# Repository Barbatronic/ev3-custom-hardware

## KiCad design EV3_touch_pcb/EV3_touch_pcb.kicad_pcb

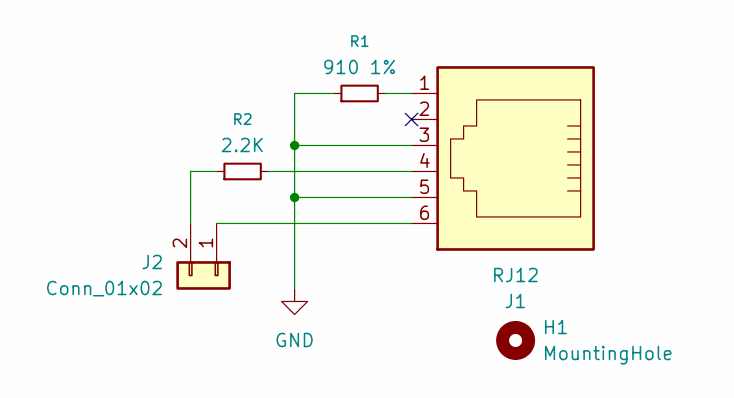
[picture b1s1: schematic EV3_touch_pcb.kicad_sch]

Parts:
H1: MountingHole; MountingHole_3.2mm_M3
J1: RJ12; RJ25_Wayconn_MJEA-660X1_Horizontal
J2: Conn_01x02; PinHeader_1x02_P2.54mm_Vertical
R1: 910 1%; R_1206_3216Metric_Pad1.30x1.75mm_HandSolder
R2: 2.2K; R_1206_3216Metric_Pad1.30x1.75mm_HandSolder

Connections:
GND: J1.3, J1.5, R1.1
unnamed: J1.1, R1.2
unnamed: J1.4, R2.2
unnamed: J1.6, J2.1
unnamed: J2.2, R2.1

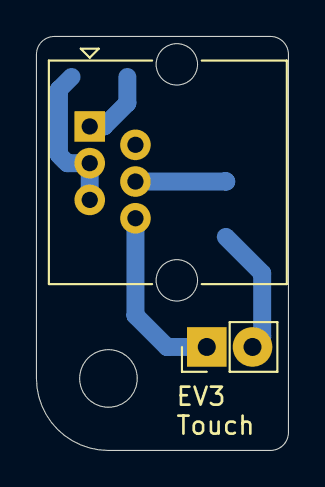
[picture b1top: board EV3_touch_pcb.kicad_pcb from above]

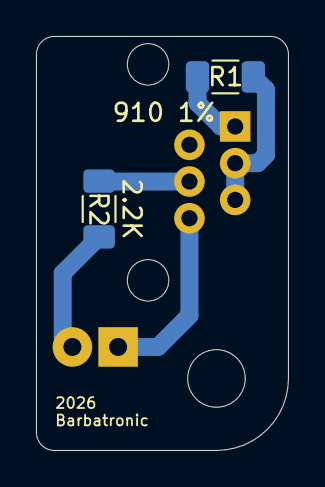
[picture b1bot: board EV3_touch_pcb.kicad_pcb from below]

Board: 2 copper layers, 14.0 x 23.0 mm, 5 parts (2 on the bottom side), 5 nets.

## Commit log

2026-02-10 intial commit
2026-02-11 optimized for F2 ultra
2026-03-05 export for fab
2026-03-05 prototype of pcb support
